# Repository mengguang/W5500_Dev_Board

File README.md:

# W5500_Dev_Board
W5500 Development Board

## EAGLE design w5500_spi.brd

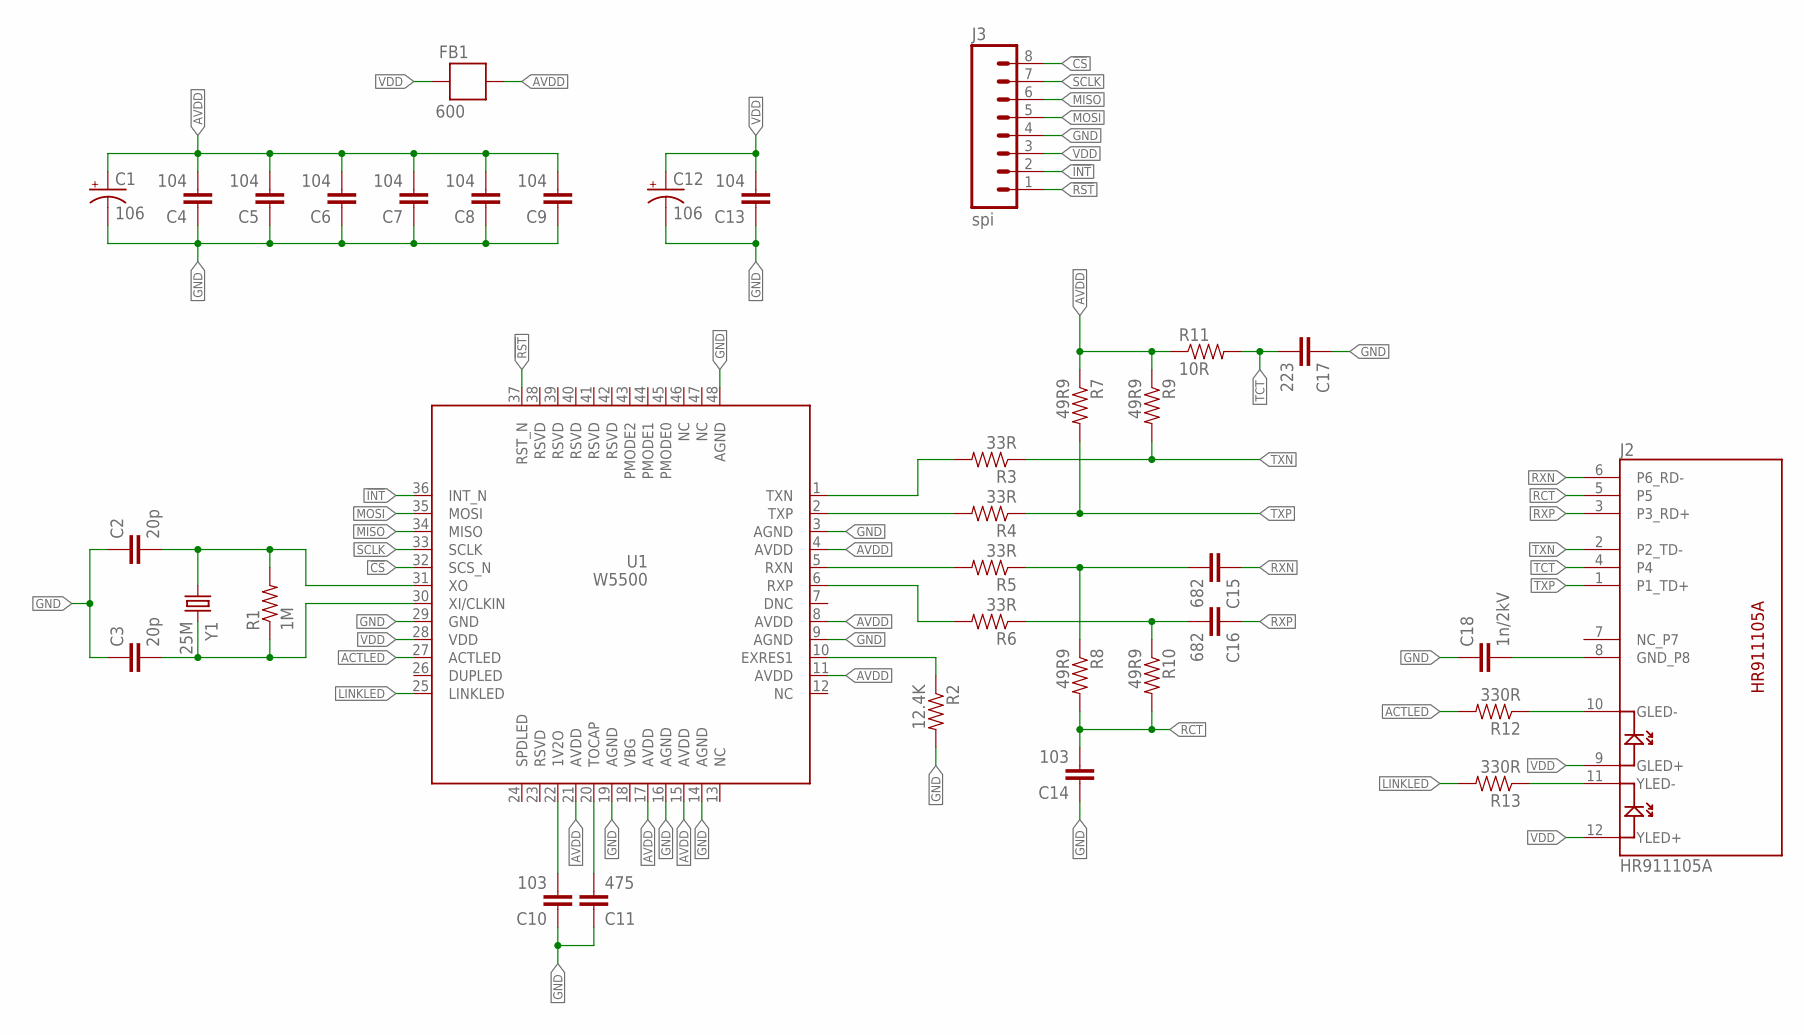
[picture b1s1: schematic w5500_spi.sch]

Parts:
C1, C12: 106; EIA3216
C2, C3: 20p; 0603-CAP
C4, C5, C6, C7, C8, C9, C13: 104; 0603-CAP
C10, C14: 103; 0603-CAP
C11: 475; 0603-CAP
C15, C16: 682; 0603-CAP
C17: 223; 0603-CAP
C18: 1n/2kV; 1206
FB1: 600; 0805
J2: HR911105A
J3: spi; 1X08_PIN1_NO_SILK
R1: 1M; 0603-RES
R2: 12.4K; 0603-RES
R3, R4, R5, R6: 33R; 0603-RES
R7, R8, R9, R10: 49R9; 0603-RES
R11: 10R; 0603-RES
R12, R13: 330R; 0603-RES
U1: W5500; LQFP-48
Y1: 25M; HC49US

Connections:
!CS: J3.8, U1.32 (SCS_N)
!INT: J3.2, U1.36 (INT_N)
!RST: J3.1, U1.37 (RST_N)
ACTLED: R12.2, U1.27 (ACTLED)
AVDD: C1.A (+), C4.2, C5.2, C6.2, C7.2, C8.2, C9.2, FB1.1, R7.1, R9.1, R11.1, U1.4 (AVDD), U1.8 (AVDD), U1.11 (AVDD), U1.15 (AVDD), U1.17 (AVDD), U1.21 (AVDD)
GND: C1.C (-), C2.1, C3.1, C4.1, C5.1, C6.1, C7.1, C8.1, C9.1, C10.1, C11.1, C12.C (-), C13.1, C14.1, C17.1, C18.1, J3.4, R2.2, U1.3 (AGND), U1.9 (AGND), U1.14 (AGND), U1.16 (AGND), U1.19 (AGND), U1.29 (GND), U1.48 (AGND)
LINKLED: R13.2, U1.25 (LINKLED)
MISO: J3.6, U1.34 (MISO)
MOSI: J3.5, U1.35 (MOSI)
unnamed: C2.2, R1.2, U1.31 (XO), Y1.1
unnamed: C10.2, U1.22 (1V2O)
unnamed: C11.2, U1.20 (TOCAP)
unnamed: C3.2, R1.1, U1.30 (XI/CLKIN), Y1.2
unnamed: R2.1, U1.10 (EXRES1)
unnamed: J2.10 (GLED-), R12.1
unnamed: J2.11 (YLED-), R13.1
unnamed: R3.2, U1.1 (TXN)
unnamed: R4.2, U1.2 (TXP)
unnamed: R5.2, U1.5 (RXN)
unnamed: R6.2, U1.6 (RXP)
unnamed: C18.2, J2.8 (GND_P8)
unnamed: C15.2, R5.1, R8.1
unnamed: C16.2, R6.1, R10.1
RCT: C14.2, J2.5, R8.2, R10.2
RXN: C15.1, J2.6 (P6_RD-)
RXP: C16.1, J2.3 (P3_RD+)
SCLK: J3.7, U1.33 (SCLK)
TCT: C17.2, J2.4, R11.2
TXN: J2.2 (P2_TD-), R3.1, R9.2
TXP: J2.1 (P1_TD+), R4.1, R7.2
VDD: C12.A (+), C13.2, FB1.2, J2.9 (GLED+), J2.12 (YLED+), J3.3, U1.28 (VDD)

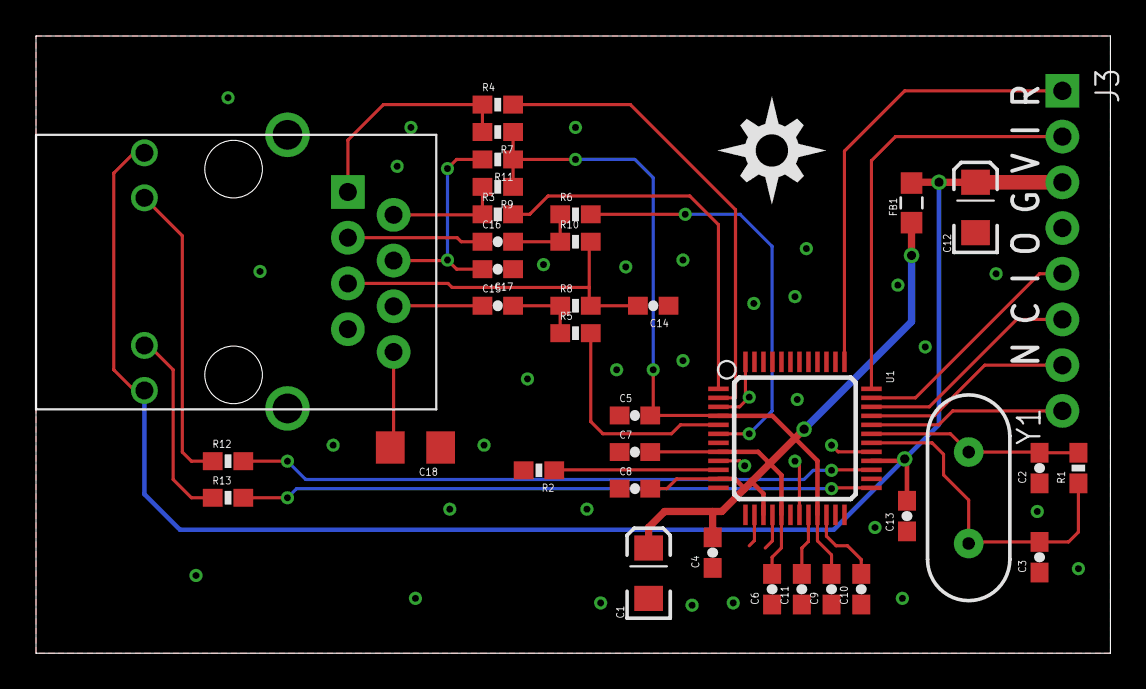
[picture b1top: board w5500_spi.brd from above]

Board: 2 copper layers, 59.7 x 34.3 mm, 37 parts (0 on the bottom side), 31 nets.

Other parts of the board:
U$1: DIYNOVA_LOGO

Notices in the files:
parts and their libraries:
DECADE-libraries20151104: Licensing: Creative Commons ShareAlike 4.0 International - https://creativecommons.org/licenses/by-sa/4.0
